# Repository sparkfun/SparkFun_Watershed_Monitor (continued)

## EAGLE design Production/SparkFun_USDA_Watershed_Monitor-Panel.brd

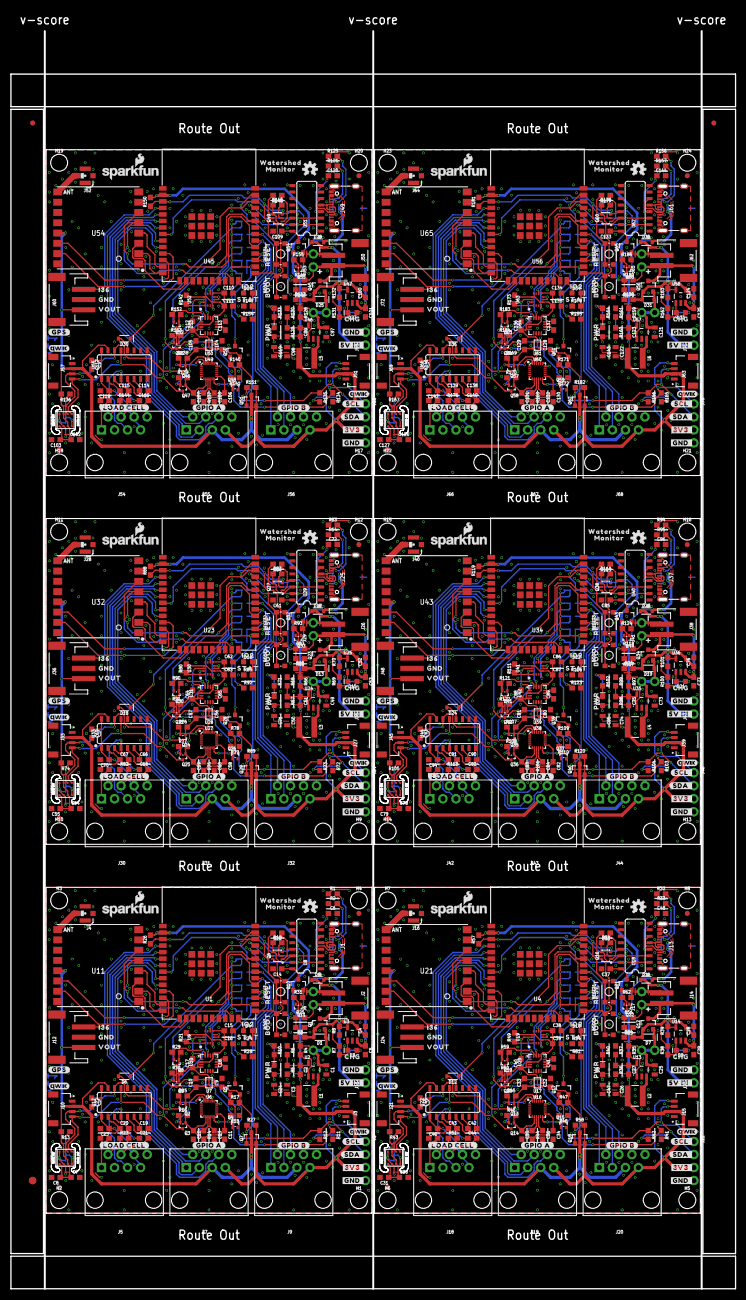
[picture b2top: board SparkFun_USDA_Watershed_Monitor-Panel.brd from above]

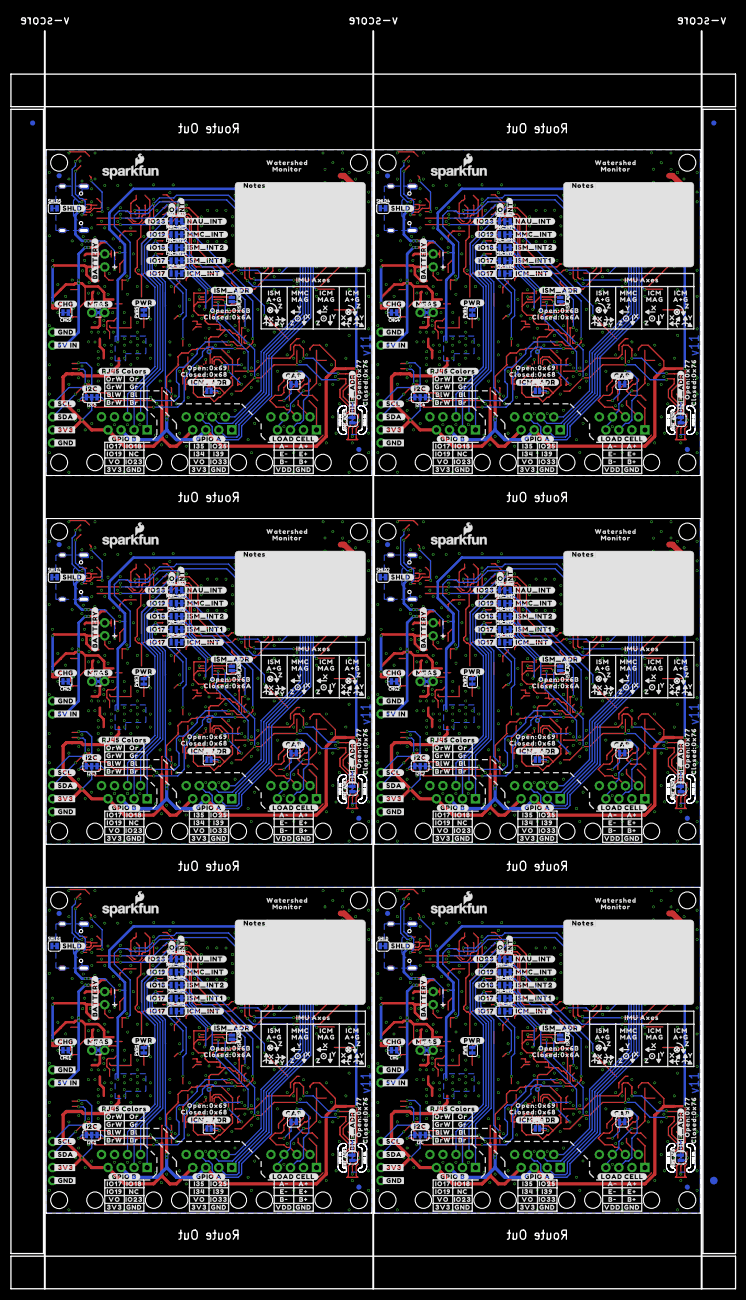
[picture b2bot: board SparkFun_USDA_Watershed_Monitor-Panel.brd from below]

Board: 2 copper layers, 141.2 x 245.1 mm, 1488 parts (711 on the bottom side), 522 nets.

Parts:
BME_ADR, BME_ADR1, BME_ADR2, BME_ADR3, BME_ADR4, BME_ADR5: JUMPER-SMT_2_NC_TRACE_SILK; SMT-JUMPER_2_NC_TRACE_SILK
BOOT, BOOT1, BOOT2, BOOT3, BOOT4, BOOT5: MOMENTARY-SWITCH-SPST-SMD-4.6X2.8MM; TACTILE_SWITCH_SMD_4.6X2.8MM
C1, C3, C24, C25, C26, C47, C49, C50, C71, C73, C74, C95, C97, C98, C119, C121, C122, C143: 22uF; 0805
C2, C27, C51, C75, C99, C123: 22pF; 0603
C4, C5, C28, C29, C52, C53, C76, C77, C100, C101, C124, C125: 4.7uF; 0603
C6, C48, C72, C96, C120, C144: 10nF; 0603
C7, C8, C11, C12, C13, C14, C19, C20, C22, C30, C31, C34, C35, C36, C37, C42, C43, C45, C54, C55, C58, C59, C60, C61, C66, C67, C69, C78, C79, C82, C83, C84, C85, C90, C91, C93, C102, C103, C106, C107, C108, C109, C114, C115, C117, C126, C127, C130, C131, C132, C133, C138, C139, C141: 0.1uF; 0603
C9, C10, C32, C33, C56, C57, C80, C81, C104, C105, C128, C129: 1.0uF; 0603
C15, C16, C17, C18, C38, C39, C40, C41, C62, C63, C64, C65, C86, C87, C88, C89, C110, C111, C112, C113, C134, C135, C136, C137: DNP; 0603
C21, C44, C68, C92, C116, C140: 330pF; 0603
C23, C46, C70, C94, C118, C142: 10uF; 0603
CHG, CHG1, CHG2, CHG3, CHG4, CHG5: JUMPER-SMT_2_NC_TRACE_SILK; SMT-JUMPER_2_NC_TRACE_SILK
D1, D5, D6, D7, D11, D12, D13, D17, D18, D19, D23, D24, D25, D29, D30, D31, D35, D36: 1A/23V/620mV; SOD-323
D2, D8, D14, D20, D26, D32: DNP; LED-0603
D3, D9, D15, D21, D27, D33: Yellow; LED-0603
D4, D10, D16, D22, D28, D34: BLUE; LED-0603
E$1, E$2, E$3, E$4: FIDUCIAL-1X2
E$5, E$6: FIDUCIAL-1.5X3
FD1, FD2, FD3, FD4, FD5, FD6, FD7, FD8, FD9, FD10, FD11, FD12, FD13, FD14, FD15, FD16, FD17, FD18, FD19, FD20, FD21, FD22, FD23, FD24: FIDUCIAL1X2; FIDUCIAL-1X2
H1, H2, H3, H4, H5, H6, H7, H8, H9, H10, H11, H12, H13, H14, H15, H16, H17, H18, H19, H20, H21, H22, H23, H24: STAND-OFF
I2C, I2C1, I2C2, I2C3, I2C4, I2C5: JUMPER-SMT_3_2-NC_TRACE_SILK; SMT-JUMPER_3_2-NC_TRACE_SILK
ICM_ADR, ICM_ADR1, ICM_ADR2, ICM_ADR3, ICM_ADR4, ICM_ADR5: JUMPER-SMT_2_NO_SILK; SMT-JUMPER_2_NO_SILK
ICM_INT, ICM_INT1, ICM_INT2, ICM_INT3, ICM_INT4, ICM_INT5: JUMPER-SMT_3_1-NC_TRACE_SILK; SMT-JUMPER_3_1-NC_TRACE_SILK
ISM_ADR, ISM_ADR1, ISM_ADR2, ISM_ADR3, ISM_ADR4, ISM_ADR5: JUMPER-SMT_2_NO_SILK; SMT-JUMPER_2_NO_SILK
ISM_INT1, ISM_INT2, ISM_INT3, ISM_INT4, ISM_INT5, ISM_INT6, ISM_INT7, ISM_INT8, ISM_INT9, ISM_INT10, ISM_INT11, ISM_INT12: JUMPER-SMT_3_1-NC_TRACE_SILK; SMT-JUMPER_3_1-NC_TRACE_SILK
J1, J13, J25, J37, J49, J61: USB-C-16P-2LAYER-PADS
J2, J14, J26, J38, J50, J62: JST-2-SMD
J3, J10, J15, J21, J27, J33, J39, J45, J51, J57, J63, J69: QWIIC_RIGHT_ANGLE; JST04_1MM_RA
J4, J16, J28, J40, J52, J64: U.FL
J5, J7, J9, J18, J19, J20, J30, J31, J32, J42, J43, J44, J54, J55, J56, J66, J67, J68: RJ45; RJ45-8
J6, J11, J17, J23, J29, J35, J41, J47, J53, J59, J65, J71: 1X02_NO_SILK
J8, J22, J34, J46, J58, J70: 1X04_NO_SILK
J12, J24, J36, J48, J60, J72: 3-PIN SMD; JST-3-SMD
L1, L2, L3, L4, L5, L6: 2.2μH; INDUCTOR_4X4MM
LOGO1, LOGO5, LOGO6, LOGO10, LOGO11, LOGO15, LOGO16, LOGO20, LOGO21, LOGO25, LOGO26, LOGO30: SFE_LOGO_NAME_FLAME.1_INCH; SFE_LOGO_NAME_FLAME_.1
LOGO2, LOGO7, LOGO12, LOGO17, LOGO22, LOGO27: OSHW-LOGOS; OSHW-LOGO-S
LOGO3, LOGO4, LOGO8, LOGO9, LOGO13, LOGO14, LOGO18, LOGO19, LOGO23, LOGO24, LOGO28, LOGO29: QWIIC_LOGO_4MM; QWIIC_4MM
MEAS, MEAS1, MEAS2, MEAS3, MEAS4, MEAS5: JUMPER-COMBO_2_NC_TRACE; COMBO-JUMPER_2_NC_TRACE
MMC_INT, MMC_INT1, MMC_INT2, MMC_INT3, MMC_INT4, MMC_INT5: JUMPER-SMT_3_1-NC_TRACE_SILK; SMT-JUMPER_3_1-NC_TRACE_SILK
NAU_CAP, NAU_CAP1, NAU_CAP2, NAU_CAP3, NAU_CAP4, NAU_CAP5: JUMPER-SMT_2_NC_TRACE_SILK; SMT-JUMPER_2_NC_TRACE_SILK
NAU_INT, NAU_INT1, NAU_INT2, NAU_INT3, NAU_INT4, NAU_INT5: JUMPER-SMT_3_1-NC_TRACE_SILK; SMT-JUMPER_3_1-NC_TRACE_SILK
PWR, PWR1, PWR2, PWR3, PWR4, PWR5: JUMPER-SMT_2_NC_TRACE_SILK; SMT-JUMPER_2_NC_TRACE_SILK
Q1, Q5, Q7, Q10, Q12, Q17, Q18, Q21, Q23, Q28, Q29, Q32, Q34, Q39, Q40, Q43, Q45, Q50, Q51, Q54, Q56, Q61, Q62, Q65: 20V/4.2A/52mΩ/1.4W; SOT23-3
Q2, Q3, Q4, Q8, Q9, Q11, Q13, Q14, Q15, Q19, Q20, Q22, Q24, Q25, Q26, Q30, Q31, Q33, Q35, Q36, Q37, Q41, Q42, Q44, Q46, Q47, Q48, Q52, Q53, Q55, Q57, Q58, Q59, Q63, Q64, Q66: 20V/0.2A/8MHz/1.2Ω/1Vth; SOT-416FL
Q6, Q16, Q27, Q38, Q49, Q60: SC70-6
R1, R2, R32, R33, R63, R64, R94, R95, R125, R126, R156, R157: 5.1k; 0603
R3, R4, R6, R9, R13, R14, R17, R18, R25, R26, R27, R28, R31, R34, R35, R37, R43, R44, R47, R48, R55, R56, R57, R58, R61, R62, R65, R66, R68, R74, R75, R78, R79, R86, R87, R88, R89, R92, R93, R96, R97, R99, R105, R106, R109, R110, R117, R118, R119, R120, R123, R124, R127, R128, R130, R136, R137, R140, R141, R148, R149, R150, R151, R154, R155, R158, R159, R161, R167, R168, R171, R172, R179, R180, R181, R182, R185, R186: 100k; 0603
R5, R36, R67, R98, R129, R160: 453k; 0603
R7, R38, R69, R100, R131, R162: 4.7k; 0603
R8, R11, R12, R15, R16, R24, R29, R30, R39, R41, R42, R45, R46, R54, R59, R60, R70, R72, R73, R76, R77, R85, R90, R91, R101, R103, R104, R107, R108, R116, R121, R122, R132, R134, R135, R138, R139, R147, R152, R153, R163, R165, R166, R169, R170, R178, R183, R184: 2.2k; 0603
R10, R21, R40, R49, R71, R80, R102, R111, R133, R142, R164, R173: DNP; 0603
R19, R20, R52, R53, R83, R84, R114, R115, R145, R146, R176, R177: 10k; 0603
R22, R23, R50, R51, R81, R82, R112, R113, R143, R144, R174, R175: 47; 0603
RESET, RESET1, RESET2, RESET3, RESET4, RESET5: MOMENTARY-SWITCH-SPST-SMD-4.6X2.8MM; TACTILE_SWITCH_SMD_4.6X2.8MM
SHLD, SHLD1, SHLD2, SHLD3, SHLD4, SHLD5: JUMPER-SMT_2_NC_TRACE_SILK; SMT-JUMPER_2_NC_TRACE_SILK
TP1, TP2, TP3, TP4, TP5, TP6: TEST-POINT3X4; PAD.03X.04
U1, U4, U23, U34, U45, U56: ESP-WROOM-3232D; ESP-WROOM-32D
U2, U13, U24, U35, U46, U57: AP3429A; SOT23-5
U3, U14, U25, U36, U47, U58: MCP73831; SOT23-5
U5, U15, U26, U37, U48, U59: BME680; LGA3.0X3.0
U6, U16, U27, U38, U49, U60: 9DoF IMU; QFN24-3X3-ICM-20948
U7, U17, U28, U39, U50, U61: 1.8V/100mA; SC70
U8, U18, U29, U40, U51, U62: CH340C; SO016
U9, U19, U30, U41, U52, U63: DNP; LGA-14L
U10, U20, U31, U42, U53, U64: DNP; LGA-16-3X3MM-4X4PINS
U11, U21, U32, U43, U54, U65: RFM9XRFM95; RFM95
U12, U22, U33, U44, U55, U66: NAU7802SOIC; SO16
U$1, U$2, U$115, U$196, U$243, U$317, U$364, U$438, U$485, U$559, U$606, U$680: WATERSHED0
U$3, U$49, U$116, U$197, U$244, U$318, U$365, U$439, U$486, U$560, U$607, U$681: MONITOR0
U$4, U$8, U$11, U$147, U$148, U$150, U$268, U$269, U$271, U$389, U$390, U$392, U$510, U$511, U$513, U$631, U$632, U$634: GND0
U$5, U$67, U$170, U$239, U$291, U$360, U$412, U$481, U$533, U$602, U$654, U$723: #IO17#0
U$6, U$79, U$180, U$182, U$301, U$303, U$422, U$424, U$543, U$545, U$664, U$666: #GND_#0
U$7, U$80, U$181, U$183, U$302, U$304, U$423, U$425, U$544, U$546, U$665, U$667: #_GND#0
U$9, U$63, U$245, U$366, U$487, U$608: #MEAS#0
U$10, U$24, U$149, U$241, U$270, U$362, U$391, U$483, U$512, U$604, U$633, U$725: 3V30
U$12, U$152, U$273, U$394, U$515, U$636: A#0
U$13, U$151, U$272, U$393, U$514, U$635: VDD0
U$14, U$90, U$246, U$367, U$488, U$609: #CHG#0
U$15, U$91, U$247, U$368, U$489, U$610: #I2C#0
U$16, U$92, U$248, U$369, U$490, U$611: CHG0
U$17, U$93, U$249, U$370, U$491, U$612: #CAP#0
U$18, U$97, U$250, U$371, U$492, U$613: #BME_ADR#0
U$19, U$98, U$251, U$372, U$493, U$614: #ICM_ADR#0
U$20, U$99, U$252, U$373, U$494, U$615: #ISM_ADR#0
U$21, U$101, U$253, U$374, U$495, U$616: #BATTERY#0
U$22, U$107, U$254, U$375, U$496, U$617: #SHLD#0
U$23, U$234, U$355, U$476, U$597, U$718: I360
U$25, U$69, U$238, U$242, U$359, U$363, U$480, U$484, U$601, U$605, U$722, U$726: VO0
U$26, U$235, U$356, U$477, U$598, U$719: VOUT0
U$27, U$108, U$255, U$376, U$497, U$618: RESET0
U$28, U$109, U$256, U$377, U$498, U$619: BOOT0
U$29, U$114, U$257, U$378, U$499, U$620: PWR0
U$30, U$129, U$258, U$379, U$500, U$621: STAT0
U$31, U$130, U$259, U$380, U$501, U$622: IO20
U$32, U$131, U$260, U$381, U$502, U$623: ORW0
U$33, U$132, U$261, U$382, U$503, U$624: OR0
U$34, U$133, U$262, U$383, U$504, U$625: GRW0
U$35, U$134, U$263, U$384, U$505, U$626: GR0
U$36, U$135, U$264, U$385, U$506, U$627: BLW0
U$37, U$136, U$265, U$386, U$507, U$628: BL0
U$38, U$145, U$266, U$387, U$508, U$629: BRW0
U$39, U$146, U$267, U$388, U$509, U$630: BR0
U$40, U$153, U$274, U$395, U$516, U$637: A#1
U$41, U$154, U$275, U$396, U$517, U$638: B#0
U$42, U$155, U$276, U$397, U$518, U$639: B#1
U$43, U$156, U$277, U$398, U$519, U$640: E#0
U$44, U$157, U$278, U$399, U$520, U$641: E#1
U$45, U$158, U$279, U$400, U$521, U$642: #RJ45_COLORS#0
U$46, U$159, U$280, U$401, U$522, U$643: #PWR#0
U$47, U$184, U$305, U$426, U$547, U$668: #3V3_#0
U$48, U$185, U$306, U$427, U$548, U$669: #SDA_#0
U$50, U$55, U$190, U$193, U$311, U$314, U$432, U$435, U$553, U$556, U$674, U$677: #LOAD_CELL#0
U$51, U$86, U$191, U$194, U$312, U$315, U$433, U$436, U$554, U$557, U$675, U$678: #GPIO_A#0
U$52, U$160, U$281, U$402, U$523, U$644: IO250
U$53, U$87, U$192, U$195, U$313, U$316, U$434, U$437, U$555, U$558, U$676, U$679: #GPIO_B#0
U$54, U$161, U$282, U$403, U$524, U$645: IO330
U$56, U$186, U$307, U$428, U$549, U$670: #SCL_#0
U$57, U$198, U$319, U$440, U$561, U$682: NC0
U$58, U$162, U$283, U$404, U$525, U$646: IO170
U$59, U$163, U$284, U$405, U$526, U$647: IO180
U$60, U$164, U$285, U$406, U$527, U$648: IO190
U$61, U$165, U$286, U$407, U$528, U$649: I340
U$62, U$166, U$287, U$408, U$529, U$650: I350
U$64, U$167, U$288, U$409, U$530, U$651: I390
U$65, U$168, U$289, U$410, U$531, U$652: #IO19#0
U$66, U$169, U$290, U$411, U$532, U$653: #IO18#0
U$68, U$240, U$361, U$482, U$603, U$724: #IO23#0
U$70, U$171, U$292, U$413, U$534, U$655: #NAU_INT#0
U$71, U$172, U$293, U$414, U$535, U$656: #MMC_INT#0
U$72, U$173, U$294, U$415, U$536, U$657: #ISM_INT2#0
U$73, U$174, U$295, U$416, U$537, U$658: #ISM_INT1#0
U$74, U$175, U$296, U$417, U$538, U$659: #ICM_INT#0
U$75, U$176, U$297, U$418, U$539, U$660: #IO#0
U$76, U$177, U$298, U$419, U$540, U$661: ##INT##0
U$77, U$178, U$299, U$420, U$541, U$662: #NOTES#0
U$78, U$179, U$300, U$421, U$542, U$663: IO230
U$81, U$187, U$308, U$429, U$550, U$671: #_SCL#1
U$82, U$121, U$125, U$201, U$205, U$209, U$322, U$326, U$330, U$443, U$447, U$451, U$564, U$568, U$572, U$685, U$689, U$693: OPEN#0
U$83, U$122, U$126, U$202, U$206, U$210, U$323, U$327, U$331, U$444, U$448, U$452, U$565, U$569, U$573, U$686, U$690, U$694: CLOSED#0
U$84, U$188, U$309, U$430, U$551, U$672: #_SDA#2
U$85, U$189, U$310, U$431, U$552, U$673: #_3V3#0
U$88, U$236, U$357, U$478, U$599, U$720: #GPS#0
U$89, U$237, U$358, U$479, U$600, U$721: GND3
U$94, U$100, U$104, U$138, U$213, U$221, U$228, U$231, U$334, U$342, U$349, U$352, U$455, U$463, U$470, U$473, U$576, U$584, U$591, U$594, U$697, U$705, U$712, U$715: X0
U$95, U$102, U$105, U$139, U$214, U$222, U$229, U$232, U$335, U$343, U$350, U$353, U$456, U$464, U$471, U$474, U$577, U$585, U$592, U$595, U$698, U$706, U$713, U$716: Y0
U$96, U$103, U$106, U$140, U$215, U$223, U$230, U$233, U$336, U$344, U$351, U$354, U$457, U$465, U$472, U$475, U$578, U$586, U$593, U$596, U$699, U$707, U$714, U$717: Z0
U$110, U$137, U$216, U$220, U$337, U$341, U$458, U$462, U$579, U$583, U$700, U$704: ICM0
U$111, U$217, U$338, U$459, U$580, U$701: ISM0
U$112, U$218, U$339, U$460, U$581, U$702: MMC0
U$113, U$219, U$340, U$461, U$582, U$703: IMU_AXES0
U$117, U$199, U$320, U$441, U$562, U$683: #5V_IN_#0
U$118, U$200, U$321, U$442, U$563, U$684: #_5V_IN#0
U$119, U$203, U$324, U$445, U$566, U$687: 0X770
U$120, U$204, U$325, U$446, U$567, U$688: 0X760
U$123, U$211, U$332, U$453, U$574, U$695: 0X6A0
U$124, U$212, U$333, U$454, U$575, U$696: 0X6B0
U$127, U$207, U$328, U$449, U$570, U$691: 0X690
U$128, U$208, U$329, U$450, U$571, U$692: 0X680
U$141, U$142, U$224, U$225, U$345, U$346, U$466, U$467, U$587, U$588, U$708, U$709: MAG0
U$143, U$144, U$226, U$227, U$347, U$348, U$468, U$469, U$589, U$590, U$710, U$711: A#G0

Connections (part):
1.8V: C10.1, C11.1, C12.1, Q2.1, Q3.1, R14.2, R15.2, R16.2, TP1.1, U6.8, U6.13, U6.22, U7.5
1.8V1: C33.1, C34.1, C35.1, Q13.1, Q14.1, R44.2, R45.2, R46.2, TP2.1, U16.8, U16.13, U16.22, U17.5
1.8V2: C57.1, C58.1, C59.1, Q24.1, Q25.1, R75.2, R76.2, R77.2, TP3.1, U27.8, U27.13, U27.22, U28.5
1.8V3: C81.1, C82.1, C83.1, Q35.1, Q36.1, R106.2, R107.2, R108.2, TP4.1, U38.8, U38.13, U38.22, U39.5
1.8V4: C105.1, C106.1, C107.1, Q46.1, Q47.1, R137.2, R138.2, R139.2, TP5.1, U49.8, U49.13, U49.22, U50.5
1.8V5: C129.1, C130.1, C131.1, Q57.1, Q58.1, R168.2, R169.2, R170.2, TP6.1, U60.8, U60.13, U60.22, U61.5
3.3V: C2.2, C3.1, C24.1, D2.A, I2C.2, J3.2, J7.7, J8.3, J9.7, L1.P$2, Q7.2, Q10.2, R5.2, R26.2, R27.2, R31.2, U1.2
3.3V1: C26.1, C27.2, C47.1, D8.A, I2C1.2, J15.2, J19.7, J20.7, J22.3, L2.P$2, Q18.2, Q21.2, R36.2, R57.2, R58.2, R62.2, U4.2
3.3V2: C50.1, C51.2, C71.1, D14.A, I2C2.2, J27.2, J31.7, J32.7, J34.3, L3.P$2, Q29.2, Q32.2, R67.2, R88.2, R89.2, R93.2, U23.2
3.3V3: C74.1, C75.2, C95.1, D20.A, I2C3.2, J39.2, J43.7, J44.7, J46.3, L4.P$2, Q40.2, Q43.2, R98.2, R119.2, R120.2, R124.2, U34.2
3.3V4: C98.1, C99.2, C119.1, D26.A, I2C4.2, J51.2, J55.7, J56.7, J58.3, L5.P$2, Q51.2, Q54.2, R129.2, R150.2, R151.2, R155.2, U45.2
3.3V5: C122.1, C123.2, C143.1, D32.A, I2C5.2, J63.2, J67.7, J68.7, J70.3, L6.P$2, Q62.2, Q65.2, R160.2, R181.2, R182.2, R186.2, U56.2
3V3_EN: R4.2, U2.1
3V3_EN1: R35.2, U13.1
3V3_EN2: R66.2, U24.1
3V3_EN3: R97.2, U35.1
3V3_EN4: R128.2, U46.1
3V3_EN5: R159.2, U57.1
5V: C4.1, D1.A, D5.C, J11.1, Q1.1, R3.2, R7.2, U3.4
5V1: C28.1, D7.A, D11.C, J23.1, Q12.1, R34.2, R38.2, U14.4
5V2: C52.1, D13.A, D17.C, J35.1, Q23.1, R65.2, R69.2, U25.4
5V3: C76.1, D19.A, D23.C, J47.1, Q34.1, R96.2, R100.2, U36.4
5V4: C100.1, D25.A, D29.C, J59.1, Q45.1, R127.2, R131.2, U47.4
5V5: C124.1, D31.A, D35.C, J71.1, Q56.1, R158.2, R162.2, U58.4
DTR: Q6.1, R20.1, U8.13
DTR1: Q16.1, R53.1, U18.13
DTR2: Q27.1, R84.1, U29.13
DTR3: Q38.1, R115.1, U40.13
DTR4: Q49.1, R146.1, U51.13
DTR5: Q60.1, R177.1, U62.13
ESP_EN: Q6.3, R26.1, RESET.3, RESET.4, U1.3
ESP_EN1: Q16.3, R57.1, RESET1.3, RESET1.4, U4.3
ESP_EN2: Q27.3, R88.1, RESET2.3, RESET2.4, U23.3
ESP_EN3: Q38.3, R119.1, RESET3.3, RESET3.4, U34.3
ESP_EN4: Q49.3, R150.1, RESET4.3, RESET4.4, U45.3
ESP_EN5: Q60.3, R181.1, RESET5.3, RESET5.4, U56.3
ESP_I1: J19.3, U4.6
ESP_I2: J19.1, U4.7
ESP_I3: J19.6, U4.5
ESP_I4: J31.3, U23.6
ESP_I5: J31.1, U23.7
ESP_I6: J31.6, U23.5
ESP_I7: J43.3, U34.6
ESP_I8: J43.1, U34.7
ESP_I9: J43.6, U34.5
ESP_I10: J55.3, U45.6
ESP_I11: J55.1, U45.7
ESP_I12: J55.6, U45.5
ESP_I13: J67.3, U56.6
ESP_I14: J67.1, U56.7
ESP_I15: J67.6, U56.5
ESP_I34: J7.3, U1.6
ESP_I35: J7.1, U1.7
ESP_I36/GPS_TX: J12.1, U1.4
ESP_I36/GPS_TX1: J24.1, U4.4
ESP_I36/GPS_TX2: J36.1, U23.4
ESP_I36/GPS_TX3: J48.1, U34.4
ESP_I36/GPS_TX4: J60.1, U45.4
ESP_I36/GPS_TX5: J72.1, U56.4
ESP_I39: J7.6, U1.5
ESP_IO0/BOOT: BOOT.3, BOOT.4, Q6.6, U1.25
ESP_IO0/BOOT1: BOOT1.3, BOOT1.4, Q16.6, U4.25
ESP_IO0/BOOT2: BOOT2.3, BOOT2.4, Q27.6, U23.25
ESP_IO0/BOOT3: BOOT3.3, BOOT3.4, Q38.6, U34.25
ESP_IO0/BOOT4: BOOT4.3, BOOT4.4, Q49.6, U45.25
ESP_IO0/BOOT5: BOOT5.3, BOOT5.4, Q60.6, U56.25
ESP_IO1: ICM_INT1.1, ISM_INT3.1, J20.1, U4.28
ESP_IO1/ESP_TX: U1.35, U8.3
ESP_IO1/ESP_TX1: U4.35, U18.3
ESP_IO1/ESP_TX2: U23.35, U29.3
ESP_IO1/ESP_TX3: U34.35, U40.3
ESP_IO1/ESP_TX4: U45.35, U51.3
ESP_IO1/ESP_TX5: U56.35, U62.3
ESP_IO2: ISM_INT4.1, J20.2, U4.30
ESP_IO2/STAT: D4.A, U1.24
ESP_IO2/STAT1: D10.A, U4.24
ESP_IO2/STAT2: D16.A, U23.24
ESP_IO2/STAT3: D22.A, U34.24
ESP_IO2/STAT4: D28.A, U45.24
ESP_IO2/STAT5: D34.A, U56.24
ESP_IO3: J20.3, MMC_INT1.1, U4.31
ESP_IO3/ESP_RX: U1.34, U8.2
ESP_IO3/ESP_RX1: U4.34, U18.2
ESP_IO3/ESP_RX2: U23.34, U29.2
ESP_IO3/ESP_RX3: U34.34, U40.2
ESP_IO3/ESP_RX4: U45.34, U51.2
ESP_IO3/ESP_RX5: U56.34, U62.2
ESP_IO4: J20.4, NAU_INT1.1, U4.37
ESP_IO4/INT_COM: ICM_INT.3, ISM_INT1.3, ISM_INT2.3, MMC_INT.3, NAU_INT.3, R28.1, U1.26
ESP_IO4/INT_COM1: ICM_INT1.3, ISM_INT3.3, ISM_INT4.3, MMC_INT1.3, NAU_INT1.3, R61.1, U4.26
ESP_IO4/INT_COM2: ICM_INT2.3, ISM_INT5.3, ISM_INT6.3, MMC_INT2.3, NAU_INT2.3, R92.1, U23.26
ESP_IO4/INT_COM3: ICM_INT3.3, ISM_INT7.3, ISM_INT8.3, MMC_INT3.3, NAU_INT3.3, R123.1, U34.26
ESP_IO4/INT_COM4: ICM_INT4.3, ISM_INT9.3, ISM_INT10.3, MMC_INT4.3, NAU_INT4.3, R154.1, U45.26
ESP_IO4/INT_COM5: ICM_INT5.3, ISM_INT11.3, ISM_INT12.3, MMC_INT5.3, NAU_INT5.3, R185.1, U56.26
ESP_IO5: J19.2, U4.10
ESP_IO5/!RFM_RST!: U1.29, U11.!RESET
ESP_IO5/!RFM_RST!1: U4.29, U21.!RESET
ESP_IO5/!RFM_RST!2: U23.29, U32.!RESET
ESP_IO5/!RFM_RST!3: U34.29, U43.!RESET
ESP_IO5/!RFM_RST!4: U45.29, U54.!RESET
ESP_IO5/!RFM_RST!5: U56.29, U65.!RESET
ESP_IO6: J19.4, U4.9
ESP_IO7: ICM_INT2.1, ISM_INT5.1, J32.1, U23.28
ESP_IO8: ISM_INT6.1, J32.2, U23.30
ESP_IO9: J32.3, MMC_INT2.1, U23.31
ESP_IO10: J32.4, NAU_INT2.1, U23.37
ESP_IO11: J31.2, U23.10
ESP_IO12: J31.4, U23.9
ESP_IO12/POCI: U1.14, U11.SDO
ESP_IO12/POCI1: U4.14, U21.SDO
ESP_IO12/POCI2: U23.14, U32.SDO
ESP_IO12/POCI3: U34.14, U43.SDO
ESP_IO12/POCI4: U45.14, U54.SDO
ESP_IO12/POCI5: U56.14, U65.SDO
ESP_IO13: ICM_INT3.1, ISM_INT7.1, J44.1, U34.28
ESP_IO13/PICO: U1.16, U11.SDI
ESP_IO13/PICO1: U4.16, U21.SDI
ESP_IO13/PICO2: U23.16, U32.SDI
ESP_IO13/PICO3: U34.16, U43.SDI
ESP_IO13/PICO4: U45.16, U54.SDI
ESP_IO13/PICO5: U56.16, U65.SDI
ESP_IO14: ISM_INT8.1, J44.2, U34.30
ESP_IO14/SCK: U1.13, U11.SCK
ESP_IO14/SCK1: U4.13, U21.SCK
ESP_IO14/SCK2: U23.13, U32.SCK
ESP_IO14/SCK3: U34.13, U43.SCK
ESP_IO14/SCK4: U45.13, U54.SCK
ESP_IO14/SCK5: U56.13, U65.SCK
ESP_IO15: J44.3, MMC_INT3.1, U34.31
ESP_IO15/!RFM_CS!: U1.23, U11.NSS
ESP_IO15/!RFM_CS!1: U4.23, U21.NSS
ESP_IO15/!RFM_CS!2: U23.23, U32.NSS
ESP_IO15/!RFM_CS!3: U34.23, U43.NSS
ESP_IO15/!RFM_CS!4: U45.23, U54.NSS
ESP_IO15/!RFM_CS!5: U56.23, U65.NSS
ESP_IO16: J44.4, NAU_INT3.1, U34.37
ESP_IO16/!VOUT_EN!: Q7.1, R27.1, U1.27
ESP_IO16/!VOUT_EN!1: Q18.1, R58.1, U4.27
ESP_IO16/!VOUT_EN!2: Q29.1, R89.1, U23.27
ESP_IO16/!VOUT_EN!3: Q40.1, R120.1, U34.27
ESP_IO16/!VOUT_EN!4: Q51.1, R151.1, U45.27
ESP_IO16/!VOUT_EN!5: Q62.1, R182.1, U56.27
ESP_IO17: ICM_INT.1, ISM_INT1.1, J9.1, U1.28
ESP_IO18: ISM_INT2.1, J9.2, U1.30
ESP_IO19: J9.3, MMC_INT.1, U1.31
ESP_IO20: J43.2, U34.10
ESP_IO21: J43.4, U34.9
ESP_IO21/SDA: J3.3, J8.2, Q8.3, R12.1, U1.33
ESP_IO21/SDA1: J15.3, J22.2, Q19.3, R42.1, U4.33
ESP_IO21/SDA2: J27.3, J34.2, Q30.3, R73.1, U23.33
ESP_IO21/SDA3: J39.3, J46.2, Q41.3, R104.1, U34.33
ESP_IO21/SDA4: J51.3, J58.2, Q52.3, R135.1, U45.33
ESP_IO21/SDA5: J63.3, J70.2, Q63.3, R166.1, U56.33
ESP_IO22: ICM_INT4.1, ISM_INT9.1, J56.1, U45.28
ESP_IO22/SCL: J3.4, J8.1, Q9.3, R11.1, U1.36
ESP_IO22/SCL1: J15.4, J22.1, Q20.3, R41.1, U4.36
ESP_IO22/SCL2: J27.4, J34.1, Q31.3, R72.1, U23.36
ESP_IO22/SCL3: J39.4, J46.1, Q42.3, R103.1, U34.36
ESP_IO22/SCL4: J51.4, J58.1, Q53.3, R134.1, U45.36
ESP_IO22/SCL5: J63.4, J70.1, Q64.3, R165.1, U56.36
ESP_IO23: J9.4, NAU_INT.1, U1.37
ESP_IO24: ISM_INT10.1, J56.2, U45.30
ESP_IO25: J7.2, U1.10
ESP_IO26: J56.3, MMC_INT4.1, U45.31
ESP_IO26/RFM_IO1: U1.11, U11.DIO1
ESP_IO26/RFM_IO2: U4.11, U21.DIO1
ESP_IO26/RFM_IO3: U23.11, U32.DIO1
ESP_IO26/RFM_IO4: U34.11, U43.DIO1
ESP_IO26/RFM_IO5: U45.11, U54.DIO1
ESP_IO26/RFM_IO6: U56.11, U65.DIO1
ESP_IO27: J56.4, NAU_INT4.1, U45.37
ESP_IO27/RFM_IO0: U1.12, U11.DIO0
ESP_IO27/RFM_IO1: U4.12, U21.DIO0
ESP_IO27/RFM_IO2: U23.12, U32.DIO0
ESP_IO27/RFM_IO3: U34.12, U43.DIO0
ESP_IO27/RFM_IO4: U45.12, U54.DIO0
ESP_IO27/RFM_IO5: U56.12, U65.DIO0
ESP_IO28: J55.2, U45.10
ESP_IO29: J55.4, U45.9
ESP_IO30: ICM_INT5.1, ISM_INT11.1, J68.1, U56.28
ESP_IO31: ISM_INT12.1, J68.2, U56.30
ESP_IO32: J68.3, MMC_INT5.1, U56.31
ESP_IO32/V_BATT_1: R55.2, R56.1, U4.8
ESP_IO32/V_BATT_2: R9.2, R25.1, U1.8
ESP_IO32/V_BATT_3: R86.2, R87.1, U23.8
ESP_IO32/V_BATT_4: R117.2, R118.1, U34.8
ESP_IO32/V_BATT_5: R148.2, R149.1, U45.8
ESP_IO32/V_BATT_6: R179.2, R180.1, U56.8
ESP_IO33: J7.4, U1.9
ESP_IO34: J68.4, NAU_INT5.1, U56.37
ESP_IO35: J67.2, U56.10
ESP_IO36: J67.4, U56.9
GND: BME_ADR.1, BOOT.1, BOOT.2, C1.2, C3.2, C4.2, C5.2, C6.2, C7.2, C8.2, C9.2, C10.2, C11.2, C12.2, C13.2, C14.2, C15.2, C16.2, C17.2, C18.2, C19.2, C22.2, C23.2, C24.2, ICM_ADR.1, ISM_ADR.1, J1.GND, J1.GND2, J2.1, J3.1, J4.1, J4.2, J5.3, J5.8, J6.2, J7.8, J8.4, J9.8, J10.1, J11.2, J12.2, PWR.1, Q4.2, Q11.2, R1.1, R2.1, R3.1, R6.1, R8.1, R9.1, R18.1, R24.1, R28.2, RESET.1, RESET.2, SHLD.1, U1.1, U1.15, U1.38, U1.GND, U1.GNDT1, U1.GNDT2, U1.GNDT3, U1.GNDT4, U1.GNDT5, U1.GNDT6, U1.GNDT7, U1.GNDT8, U2.2, U3.2, U5.1, U5.7, U6.18, U6.20, U7.2, U8.1, U9.P6, U9.P7, U10.9, U10.11, U11.GND@1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
GND1: BME_ADR1.1, BOOT1.1, BOOT1.2, C25.2, C26.2, C28.2, C29.2, C30.2, C31.2, C32.2, C33.2, C34.2, C35.2, C36.2, C37.2, C38.2, C39.2, C40.2, C41.2, C42.2, C45.2, C46.2, C47.2, C48.2, ICM_ADR1.1, ISM_ADR1.1, J13.GND, J13.GND2, J14.1, J15.1, J16.1, J16.2, J17.2, J18.3, J18.8, J19.8, J20.8, J21.1, J22.4, J23.2, J24.2, PWR1.1, Q15.2, Q22.2, R32.1, R33.1, R34.1, R37.1, R39.1, R48.1, R54.1, R55.1, R61.2, RESET1.1, RESET1.2, SHLD1.1, U4.1, U4.15, U4.38, U4.GND, U4.GNDT1, U4.GNDT2, U4.GNDT3, U4.GNDT4, U4.GNDT5, U4.GNDT6, U4.GNDT7, U4.GNDT8, U13.2, U14.2, U15.1, U15.7, U16.18, U16.20, U17.2, U18.1, U19.P6, U19.P7, U20.9, U20.11, U21.GND@1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
GND4: BME_ADR2.1, BOOT2.1, BOOT2.2, C49.2, C50.2, C52.2, C53.2, C54.2, C55.2, C56.2, C57.2, C58.2, C59.2, C60.2, C61.2, C62.2, C63.2, C64.2, C65.2, C66.2, C69.2, C70.2, C71.2, C72.2, ICM_ADR2.1, ISM_ADR2.1, J25.GND, J25.GND2, J26.1, J27.1, J28.1, J28.2, J29.2, J30.3, J30.8, J31.8, J32.8, J33.1, J34.4, J35.2, J36.2, PWR2.1, Q26.2, Q33.2, R63.1, R64.1, R65.1, R68.1, R70.1, R79.1, R85.1, R86.1, R92.2, RESET2.1, RESET2.2, SHLD2.1, U23.1, U23.15, U23.38, U23.GND, U23.GNDT1, U23.GNDT2, U23.GNDT3, U23.GNDT4, U23.GNDT5, U23.GNDT6, U23.GNDT7, U23.GNDT8, U24.2, U25.2, U26.1, U26.7, U27.18, U27.20, U28.2, U29.1, U30.P6, U30.P7, U31.9, U31.11, U32.GND@1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
GND6: BME_ADR3.1, BOOT3.1, BOOT3.2, C73.2, C74.2, C76.2, C77.2, C78.2, C79.2, C80.2, C81.2, C82.2, C83.2, C84.2, C85.2, C86.2, C87.2, C88.2, C89.2, C90.2, C93.2, C94.2, C95.2, C96.2, ICM_ADR3.1, ISM_ADR3.1, J37.GND, J37.GND2, J38.1, J39.1, J40.1, J40.2, J41.2, J42.3, J42.8, J43.8, J44.8, J45.1, J46.4, J47.2, J48.2, PWR3.1, Q37.2, Q44.2, R94.1, R95.1, R96.1, R99.1, R101.1, R110.1, R116.1, R117.1, R123.2, RESET3.1, RESET3.2, SHLD3.1, U34.1, U34.15, U34.38, U34.GND, U34.GNDT1, U34.GNDT2, U34.GNDT3, U34.GNDT4, U34.GNDT5, U34.GNDT6, U34.GNDT7, U34.GNDT8, U35.2, U36.2, U37.1, U37.7, U38.18, U38.20, U39.2, U40.1, U41.P6, U41.P7, U42.9, U42.11, U43.GND@1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
GND8: BME_ADR4.1, BOOT4.1, BOOT4.2, C97.2, C98.2, C100.2, C101.2, C102.2, C103.2, C104.2, C105.2, C106.2, C107.2, C108.2, C109.2, C110.2, C111.2, C112.2, C113.2, C114.2, C117.2, C118.2, C119.2, C120.2, ICM_ADR4.1, ISM_ADR4.1, J49.GND, J49.GND2, J50.1, J51.1, J52.1, J52.2, J53.2, J54.3, J54.8, J55.8, J56.8, J57.1, J58.4, J59.2, J60.2, PWR4.1, Q48.2, Q55.2, R125.1, R126.1, R127.1, R130.1, R132.1, R141.1, R147.1, R148.1, R154.2, RESET4.1, RESET4.2, SHLD4.1, U45.1, U45.15, U45.38, U45.GND, U45.GNDT1, U45.GNDT2, U45.GNDT3, U45.GNDT4, U45.GNDT5, U45.GNDT6, U45.GNDT7, U45.GNDT8, U46.2, U47.2, U48.1, U48.7, U49.18, U49.20, U50.2, U51.1, U52.P6, U52.P7, U53.9, U53.11, U54.GND@1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
GND10: BME_ADR5.1, BOOT5.1, BOOT5.2, C121.2, C122.2, C124.2, C125.2, C126.2, C127.2, C128.2, C129.2, C130.2, C131.2, C132.2, C133.2, C134.2, C135.2, C136.2, C137.2, C138.2, C141.2, C142.2, C143.2, C144.2, ICM_ADR5.1, ISM_ADR5.1, J61.GND, J61.GND2, J62.1, J63.1, J64.1, J64.2, J65.2, J66.3, J66.8, J67.8, J68.8, J69.1, J70.4, J71.2, J72.2, PWR5.1, Q59.2, Q66.2, R156.1, R157.1, R158.1, R161.1, R163.1, R172.1, R178.1, R179.1, R185.2, RESET5.1, RESET5.2, SHLD5.1, U56.1, U56.15, U56.38, U56.GND, U56.GNDT1, U56.GNDT2, U56.GNDT3, U56.GNDT4, U56.GNDT5, U56.GNDT6, U56.GNDT7, U56.GNDT8, U57.2, U58.2, U59.1, U59.7, U60.18, U60.20, U61.2, U62.1, U63.P6, U63.P7, U64.9, U64.11, U65.GND@1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
ICM_INT: ICM_INT.2, Q5.3
ICM_INT1: ICM_INT1.2, Q17.3
ICM_INT2: ICM_INT2.2, Q28.3
ICM_INT3: ICM_INT3.2, Q39.3
ICM_INT4: ICM_INT4.2, Q50.3
ICM_INT5: ICM_INT5.2, Q61.3
ICM_INT_1V1: Q15.1, R48.2, U16.12
ICM_INT_1V2: Q26.1, R79.2, U27.12
ICM_INT_1V3: Q37.1, R110.2, U38.12
ICM_INT_1V4: Q48.1, R141.2, U49.12
ICM_INT_1V5: Q59.1, R172.2, U60.12
ICM_INT_1V8: Q4.1, R18.2, U6.12
ISM_INT1: ISM_INT1.2, U9.P4
ISM_INT2: ISM_INT2.2, U9.P9
ISM_INT3: ISM_INT4.2, U19.P9
ISM_INT4: ISM_INT3.2, U19.P4
ISM_INT5: ISM_INT6.2, U30.P9
ISM_INT6: ISM_INT5.2, U30.P4
ISM_INT7: ISM_INT8.2, U41.P9
ISM_INT8: ISM_INT7.2, U41.P4
ISM_INT9: ISM_INT10.2, U52.P9
ISM_INT10: ISM_INT9.2, U52.P4
ISM_INT11: ISM_INT12.2, U63.P9
ISM_INT12: ISM_INT11.2, U63.P4
MMC_INT: MMC_INT.2, U10.15
MMC_INT1: MMC_INT1.2, U20.15
MMC_INT2: MMC_INT2.2, U31.15
MMC_INT3: MMC_INT3.2, U42.15
MMC_INT4: MMC_INT4.2, U53.15
MMC_INT5: MMC_INT5.2, U64.15
unnamed: D4.C, R24.2
unnamed: L1.P$1, U2.3
unnamed: C1.1, MEAS.2, MEAS.4, R4.1, U2.4
unnamed: J1.B5, R1.2
unnamed: J1.A5, R2.2
unnamed: D1.C, MEAS.1, MEAS.3, Q1.2
unnamed: C2.1, R5.1, R6.2, U2.5
unnamed: D3.C, U3.1
unnamed: CHG.2, D3.A
unnamed: CHG.1, R7.1
unnamed: R8.2, U3.5
unnamed: C6.1, U8.4
unnamed: BME_ADR.2, R13.1, U5.5
unnamed: C13.1, U6.10
unnamed: I2C.1, R12.2
unnamed: I2C.3, R11.2
unnamed: ICM_ADR.2, R14.1, U6.9
unnamed: Q6.5, R20.2
unnamed: Q6.2, R19.2
unnamed: C18.1, U10.10
unnamed: ISM_ADR.2, R21.1, U9.P1
unnamed: C19.1, U12.6
unnamed: D2.C, R10.2
unnamed: C21.1, NAU_CAP.1
unnamed: J4.FEED, U11.ANT
unnamed: PWR.2, R10.1
unnamed: C20.2, R23.2, U12.3
unnamed: C20.1, R22.2, U12.2
unnamed: D6.A, U12.12
unnamed: Q4.3, Q5.1, R17.1
unnamed: Q10.1, Q11.3, R31.1
unnamed: C14.1, Q10.3, U8.16
unnamed: J13.B5, R32.2
unnamed: J13.A5, R33.2
unnamed: L2.P$1, U13.3
unnamed: C25.1, MEAS1.2, MEAS1.4, R35.1, U13.4
unnamed: D7.C, MEAS1.1, MEAS1.3, Q12.2
unnamed: C27.1, R36.1, R37.2, U13.5
unnamed: D9.C, U14.1
unnamed: CHG1.2, D9.A
unnamed: CHG1.1, R38.1
unnamed: I2C1.1, R42.2
unnamed: I2C1.3, R41.2
unnamed: BME_ADR1.2, R43.1, U15.5
unnamed: C36.1, U16.10
unnamed: ICM_ADR1.2, R44.1, U16.9
unnamed: C41.1, U20.10
unnamed: ISM_ADR1.2, R49.1, U19.P1
unnamed: J16.FEED, U21.ANT
unnamed: C42.1, U22.6
unnamed: C43.2, R51.2, U22.3
unnamed: C43.1, R50.2, U22.2
unnamed: C44.1, NAU_CAP1.1
unnamed: Q16.5, R53.2
unnamed: Q16.2, R52.2
unnamed: D8.C, R40.2
unnamed: PWR1.2, R40.1
unnamed: D10.C, R54.2
unnamed: R39.2, U14.5
unnamed: C48.1, U18.4
unnamed: D12.A, U22.12
unnamed: Q15.3, Q17.1, R47.1
unnamed: Q21.1, Q22.3, R62.1
unnamed: C37.1, Q21.3, U18.16
unnamed: J25.B5, R63.2
unnamed: J25.A5, R64.2
unnamed: L3.P$1, U24.3
unnamed: C49.1, MEAS2.2, MEAS2.4, R66.1, U24.4
unnamed: D13.C, MEAS2.1, MEAS2.3, Q23.2
unnamed: C51.1, R67.1, R68.2, U24.5
unnamed: D15.C, U25.1
unnamed: CHG2.2, D15.A
unnamed: CHG2.1, R69.1
unnamed: I2C2.1, R73.2
unnamed: I2C2.3, R72.2
unnamed: BME_ADR2.2, R74.1, U26.5
unnamed: C60.1, U27.10
unnamed: ICM_ADR2.2, R75.1, U27.9
unnamed: C65.1, U31.10
unnamed: ISM_ADR2.2, R80.1, U30.P1
unnamed: J28.FEED, U32.ANT
unnamed: C66.1, U33.6
unnamed: C67.2, R82.2, U33.3
unnamed: C67.1, R81.2, U33.2
unnamed: C68.1, NAU_CAP2.1
unnamed: Q27.5, R84.2
unnamed: Q27.2, R83.2
unnamed: D14.C, R71.2
unnamed: PWR2.2, R71.1
unnamed: D16.C, R85.2
unnamed: R70.2, U25.5
unnamed: C72.1, U29.4
unnamed: D18.A, U33.12
unnamed: Q26.3, Q28.1, R78.1
unnamed: Q32.1, Q33.3, R93.1
unnamed: C61.1, Q32.3, U29.16
unnamed: J37.B5, R94.2
unnamed: J37.A5, R95.2
unnamed: L4.P$1, U35.3
unnamed: C73.1, MEAS3.2, MEAS3.4, R97.1, U35.4
unnamed: D19.C, MEAS3.1, MEAS3.3, Q34.2
unnamed: C75.1, R98.1, R99.2, U35.5
unnamed: D21.C, U36.1
unnamed: CHG3.2, D21.A
unnamed: CHG3.1, R100.1
unnamed: I2C3.1, R104.2
unnamed: I2C3.3, R103.2
unnamed: BME_ADR3.2, R105.1, U37.5
unnamed: C84.1, U38.10
unnamed: ICM_ADR3.2, R106.1, U38.9
unnamed: C89.1, U42.10
unnamed: ISM_ADR3.2, R111.1, U41.P1
unnamed: J40.FEED, U43.ANT
unnamed: C90.1, U44.6
unnamed: C91.2, R113.2, U44.3
unnamed: C91.1, R112.2, U44.2
unnamed: C92.1, NAU_CAP3.1
unnamed: Q38.5, R115.2
unnamed: Q38.2, R114.2
unnamed: D20.C, R102.2
unnamed: PWR3.2, R102.1
unnamed: D22.C, R116.2
unnamed: R101.2, U36.5
unnamed: C96.1, U40.4
unnamed: D24.A, U44.12
unnamed: Q37.3, Q39.1, R109.1
unnamed: Q43.1, Q44.3, R124.1
unnamed: C85.1, Q43.3, U40.16
unnamed: J49.B5, R125.2
unnamed: J49.A5, R126.2
unnamed: L5.P$1, U46.3
unnamed: C97.1, MEAS4.2, MEAS4.4, R128.1, U46.4
unnamed: D25.C, MEAS4.1, MEAS4.3, Q45.2
unnamed: C99.1, R129.1, R130.2, U46.5
unnamed: D27.C, U47.1
unnamed: CHG4.2, D27.A
unnamed: CHG4.1, R131.1
unnamed: I2C4.1, R135.2
unnamed: I2C4.3, R134.2
unnamed: BME_ADR4.2, R136.1, U48.5
unnamed: C108.1, U49.10
unnamed: ICM_ADR4.2, R137.1, U49.9
unnamed: C113.1, U53.10
unnamed: ISM_ADR4.2, R142.1, U52.P1
unnamed: J52.FEED, U54.ANT
unnamed: C114.1, U55.6
unnamed: C115.2, R144.2, U55.3
unnamed: C115.1, R143.2, U55.2
unnamed: C116.1, NAU_CAP4.1
unnamed: Q49.5, R146.2
unnamed: Q49.2, R145.2
unnamed: D26.C, R133.2
unnamed: PWR4.2, R133.1
unnamed: D28.C, R147.2
unnamed: R132.2, U47.5
unnamed: C120.1, U51.4
unnamed: D30.A, U55.12
unnamed: Q48.3, Q50.1, R140.1
unnamed: Q54.1, Q55.3, R155.1
unnamed: C109.1, Q54.3, U51.16
unnamed: J61.B5, R156.2
unnamed: J61.A5, R157.2
unnamed: L6.P$1, U57.3
unnamed: C121.1, MEAS5.2, MEAS5.4, R159.1, U57.4
unnamed: D31.C, MEAS5.1, MEAS5.3, Q56.2
unnamed: C123.1, R160.1, R161.2, U57.5
unnamed: D33.C, U58.1
unnamed: CHG5.2, D33.A
unnamed: CHG5.1, R162.1
unnamed: I2C5.1, R166.2
unnamed: I2C5.3, R165.2
unnamed: BME_ADR5.2, R167.1, U59.5
unnamed: C132.1, U60.10
unnamed: ICM_ADR5.2, R168.1, U60.9
unnamed: C137.1, U64.10
unnamed: ISM_ADR5.2, R173.1, U63.P1
unnamed: J64.FEED, U65.ANT
unnamed: C138.1, U66.6
unnamed: C139.2, R175.2, U66.3
unnamed: C139.1, R174.2, U66.2
unnamed: C140.1, NAU_CAP5.1
unnamed: Q60.5, R177.2
unnamed: Q60.2, R176.2
unnamed: D32.C, R164.2
unnamed: PWR5.2, R164.1
unnamed: D34.C, R178.2
unnamed: R163.2, U58.5
unnamed: C144.1, U62.4
unnamed: D36.A, U66.12
unnamed: Q59.3, Q61.1, R171.1
unnamed: Q65.1, Q66.3, R186.1
unnamed: C133.1, Q65.3, U62.16
NAU_A+: J5.2, R23.1
NAU_A+1: J18.2, R51.1
NAU_A+2: J30.2, R82.1
NAU_A+3: J42.2, R113.1
NAU_A+4: J54.2, R144.1
NAU_A+5: J66.2, R175.1
NAU_A-: J5.1, R22.1
NAU_A-1: J18.1, R50.1
NAU_A-2: J30.1, R81.1
NAU_A-3: J42.1, R112.1
NAU_A-4: J54.1, R143.1
NAU_A-5: J66.1, R174.1
NAU_B+: C21.2, J5.4, U12.5
NAU_B+1: C44.2, J18.4, U22.5
NAU_B+2: C68.2, J30.4, U33.5
NAU_B+3: C92.2, J42.4, U44.5
NAU_B+4: C116.2, J54.4, U55.5
NAU_B+5: C140.2, J66.4, U66.5
NAU_B-: J5.5, NAU_CAP.2, U12.4
NAU_B-1: J18.5, NAU_CAP1.2, U22.4
NAU_B-2: J30.5, NAU_CAP2.2, U33.4
NAU_B-3: J42.5, NAU_CAP3.2, U44.4
NAU_B-4: J54.5, NAU_CAP4.2, U55.4
NAU_B-5: J66.5, NAU_CAP5.2, U66.4
NAU_INT: D6.C, NAU_INT.2
NAU_INT1: D12.C, NAU_INT1.2
NAU_INT2: D18.C, NAU_INT2.2
NAU_INT3: D24.C, NAU_INT3.2
NAU_INT4: D30.C, NAU_INT4.2
NAU_INT5: D36.C, NAU_INT5.2
RTS: Q6.4, R19.1, U8.14
RTS1: Q16.4, R52.1, U18.14
RTS2: Q27.4, R83.1, U29.14
RTS3: Q38.4, R114.1, U40.14
RTS4: Q49.4, R145.1, U51.14
RTS5: Q60.4, R176.1, U62.14
SCL_1V1: Q14.2, R46.1, U16.23
SCL_1V2: Q25.2, R77.1, U27.23
SCL_1V3: Q36.2, R108.1, U38.23
SCL_1V4: Q47.2, R139.1, U49.23
SCL_1V5: Q58.2, R170.1, U60.23
SCL_1V8: Q3.2, R16.1, U6.23
SCL_OUT: J10.4, Q3.3, Q9.2, R30.1, U5.4, U9.P13, U10.1, U12.13
SCL_OUT1: J21.4, Q14.3, Q20.2, R60.1, U15.4, U19.P13, U20.1, U22.13
SCL_OUT2: J33.4, Q25.3, Q31.2, R91.1, U26.4, U30.P13, U31.1, U33.13
SCL_OUT3: J45.4, Q36.3, Q42.2, R122.1, U37.4, U41.P13, U42.1, U44.13
SCL_OUT4: J57.4, Q47.3, Q53.2, R153.1, U48.4, U52.P13, U53.1, U55.13
SCL_OUT5: J69.4, Q58.3, Q64.2, R184.1, U59.4, U63.P13, U64.1, U66.13
SDA_1V1: Q13.2, R45.1, U16.24
SDA_1V2: Q24.2, R76.1, U27.24
SDA_1V3: Q35.2, R107.1, U38.24
SDA_1V4: Q46.2, R138.1, U49.24
SDA_1V5: Q57.2, R169.1, U60.24
SDA_1V8: Q2.2, R15.1, U6.24
SDA_OUT: J10.3, Q2.3, Q8.2, R29.1, U5.3, U9.P14, U10.16, U12.14
SDA_OUT1: J21.3, Q13.3, Q19.2, R59.1, U15.3, U19.P14, U20.16, U22.14
SDA_OUT2: J33.3, Q24.3, Q30.2, R90.1, U26.3, U30.P14, U31.16, U33.14
SDA_OUT3: J45.3, Q35.3, Q41.2, R121.1, U37.3, U41.P14, U42.16, U44.14
SDA_OUT4: J57.3, Q46.3, Q52.2, R152.1, U48.3, U52.P14, U53.16, U55.14
SDA_OUT5: J69.3, Q57.3, Q63.2, R183.1, U59.3, U63.P14, U64.16, U66.14
SHLD: J1.SHLD1, J1.SHLD2, J1.SHLD3, J1.SHLD4, SHLD.2
SHLD1: J13.SHLD1, J13.SHLD2, J13.SHLD3, J13.SHLD4, SHLD1.2
SHLD2: J25.SHLD1, J25.SHLD2, J25.SHLD3, J25.SHLD4, SHLD2.2
SHLD3: J37.SHLD1, J37.SHLD2, J37.SHLD3, J37.SHLD4, SHLD3.2
SHLD4: J49.SHLD1, J49.SHLD2, J49.SHLD3, J49.SHLD4, SHLD4.2
SHLD5: J61.SHLD1, J61.SHLD2, J61.SHLD3, J61.SHLD4, SHLD5.2
USB_DN: J1.A7, J1.B7, U8.6
USB_DN1: J13.A7, J13.B7, U18.6
USB_DN2: J25.A7, J25.B7, U29.6
USB_DN3: J37.A7, J37.B7, U40.6
USB_DN4: J49.A7, J49.B7, U51.6
USB_DN5: J61.A7, J61.B7, U62.6
USB_DP: J1.A6, J1.B6, U8.5
USB_DP1: J13.A6, J13.B6, U18.5
USB_DP2: J25.A6, J25.B6, U29.5
USB_DP3: J37.A6, J37.B6, U40.5
USB_DP4: J49.A6, J49.B6, U51.5
USB_DP5: J61.A6, J61.B6, U62.5
VDDA: C22.1, C23.1, J5.6, J5.7, U12.1, U12.16
VDDA1: C45.1, C46.1, J18.6, J18.7, U22.1, U22.16
VDDA2: C69.1, C70.1, J30.6, J30.7, U33.1, U33.16
VDDA3: C93.1, C94.1, J42.6, J42.7, U44.1, U44.16
VDDA4: C117.1, C118.1, J54.6, J54.7, U55.1, U55.16
VDDA5: C141.1, C142.1, J66.6, J66.7, U66.1, U66.16
VOUT: C7.1, C8.1, C9.1, C15.1, C16.1, C17.1, J7.5, J9.5, J10.2, J12.3, Q5.2, Q7.3, Q8.1, Q9.1, R13.2, R17.2, R21.2, R29.2, R30.2, U5.2, U5.6, U5.8, U7.1, U7.3, U9.P5, U9.P8, U9.P12, U10.2, U10.4, U10.13, U11.3.3V, U12.15
VOUT1: C30.1, C31.1, C32.1, C38.1, C39.1, C40.1, J19.5, J20.5, J21.2, J24.3, Q17.2, Q18.3, Q19.1, Q20.1, R43.2, R47.2, R49.2, R59.2, R60.2, U15.2, U15.6, U15.8, U17.1, U17.3, U19.P5, U19.P8, U19.P12, U20.2, U20.4, U20.13, U21.3.3V, U22.15
VOUT2: C54.1, C55.1, C56.1, C62.1, C63.1, C64.1, J31.5, J32.5, J33.2, J36.3, Q28.2, Q29.3, Q30.1, Q31.1, R74.2, R78.2, R80.2, R90.2, R91.2, U26.2, U26.6, U26.8, U28.1, U28.3, U30.P5, U30.P8, U30.P12, U31.2, U31.4, U31.13, U32.3.3V, U33.15
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
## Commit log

2022-12-15 Add initial schematic and board layout
2022-12-15 Finish 90% of initial design
    Rename Eagle files to match project name
    Clean up schematic arrangement
    Finish 90% of routing (ESP32 connections will be determined later)
    Add Buzzard labels
2022-12-21 Finish initial design
    Increase board height from 2 to 2.5 inches
    Move LoRa module up, and antenna to top side of board
    Replace load cell spring terminal and GPIO header with RJ45 jacks
    Add second Qwiic connector to left side of board
    Remove fuel gauge
    Remove CHG_I jumper, and set charge current to 500mA only
2023-01-03 Cleanup design
    Connect interrupt net to IO4
    Connect V_BATT to IO32 pin through voltage divider to measure battery voltage
    Increase 3V3 trace width to 25 mils on low half of board
2023-01-10 Replace center RJ45 with header pins
    Fully populate other RJ45's with GPIO pins, leaving 2 free GPIO pins going to header pins
2023-01-10 Clean up connectors in schematic
2023-01-10 Add 5V header
    Add 5V header for power injection
    Rename V_USB net to 5V
    Add diode to USB input to protect against 5V contention
    Header took place of I2C pullups, so those got moved to other side of Qwiic connector
    Add units to measures
2023-01-12 Schematic review updates
    Add note about ICM-20948 going EOL
    Add I2C addresses of all sensors
    Add max input voltage to regulators
    Add value to 3V3 regulator
    Add boot table to auto reset
    Change power LED resistor to 1k
2023-01-13 Design review updates
    Replace "VUSB" buzzard label with "5V"
    Add test point for 1.8V net
    Nudge C22 to the left
    Add selective solder paths
    Move u.FL connector away from board edge
    Nudge GPIO lines under load cell connector to the left
2023-01-13 Move load cell connector to bottom edge
    Will help a lot with panelization
    Moved left GPIO RJ45 connector to bottom middle, and redid connections for easier routing
2023-01-13 Connect RFM95W pins
    Somebody forgot to connect them...
    Connect ESP32's IO5 and IO15 (both internally pulled high) to RFM's RESET and CS respectively
    Connect ESP32's IO26 and IO27 to RFM's IO1 and IO0 respectively (IO2 not needed for LoRa)
    ESP32's IO15, IO26, and IO27 are no longer broken out to RJ45 or headers
    Add pullup resistor to ESP_EN
2023-01-13 Design review updates
    Remove 3V3_EN and ICM's FSYNC nets (won't be used)
    Add diode to NAU_INT (chip doesn't do open-drain)
    Clarify interrupts needing to be open-drain, active high
    Fix ICM interrupt level shifter output to be high-Z when input is low (or high-Z), and drive high when input is high
    Add version number to copper
    Add silk labels to RJ45s, and dashed lines connecting pinout to color code
2023-01-13 Checklist updates
    Add measures or PTH pads
    Copy SFE logo and board name silk on back side
2023-01-13 Add MMC I2C address to schematic
2023-01-13 Fix ISM and MMC axis silk labels
    They were flipped, just swapped the names
2023-01-17 Add VOUT net for GPIO A, left Qwiic, and load cell
    Controlled by a P-channel MOSFET, had to steal GPIO16
    Also changed "5V" label to "5V IN"
2023-01-17 Add proto production files
2023-01-17 Update DNP component values and PROD_ID's
2023-03-22 Add 3-pin JST connector for GPS
2023-03-22 Connect all onboard sensors and LoRa to VOUT
    Helps achieve lower power
2023-03-23 Add level shifter circuits for I2C sensors on VOUT
    Sensors can get back powered through SDA and SCL pullups
    Added MOSFET level shifter circuits to create new SDA/SCL_OUT nets with pullups to VOUT
    Updated routing accordingly
2023-03-23 Design review updates
    Bump version number to v10
    Change BME_ADR from NO to NC
    Add I2C addresses to silk
    Remove hot warning from silk
    Add better pin 1 indicator for BBME680
    Add 100k pulldown on ESP_INT_COM net
2023-03-27 Design review updates
    Add power control to CH340 (required some components in top right corner to be rearranged)
    Nudge fiducials and OSHW logo
    Update GPS connector silk
    Update RJ45 connector "A" pinout silk to have "VO" instead of "3V3"
    Fix STAT LED measure
2023-03-27 Rearrange CH340 power control components
    Gives more space around D5, its pads were close to other GND pads
2023-03-27 Fix battery polarity silk
2023-03-27 Flip and nudge CH340 power control components
    Again...
    Gives more clearance between components and pads
2023-03-27 Reorient CAP jumper label
2023-03-28 Update power LED
    Change to new SKU
    Set as DNP
2023-03-28 Add 3V3 and VOUT to both RJ45 GPIO connectors
2023-03-28 Update GPIO net names
    Include both the ESP GPIO number, and the destination
    Required schematic to be nudged around in a couple places
2023-03-28 Reorder alternative interrupt pins
    ESP16 was shared between an alternative interrupt, and the power control
2023-03-28 Change CH340 power control to be based on VUSB instead of 5V net
2023-03-28 Update RJ45 connector silk
2023-03-29 Fix load cell B+/- pinout
    Update to match silkscreen
2023-03-29 Add note to schematic about CH340 power
2023-03-29 Add note about VOUT to schematic
    Add note instructing how to enable VOUT
    Rename net to !VOUT_EN!
2023-04-03 Checklist updates
    Add ordering instructions
    Minor silk tweaks
2023-04-03 Add v10 production files
2023-04-03 Add datasheets
2023-05-01 Change DIO-14072 for DIO-11623
2023-09-22 v11 updates
    Bump version number to v11
    Remove USDA from silkscreen
    Repanelize
2023-09-22 Update file names
    Remove USDA references
